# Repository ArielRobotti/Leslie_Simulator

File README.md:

# Leslie_Simulator

Electronic design project in Kicad commissioned by jayluo1 (Fiverr)

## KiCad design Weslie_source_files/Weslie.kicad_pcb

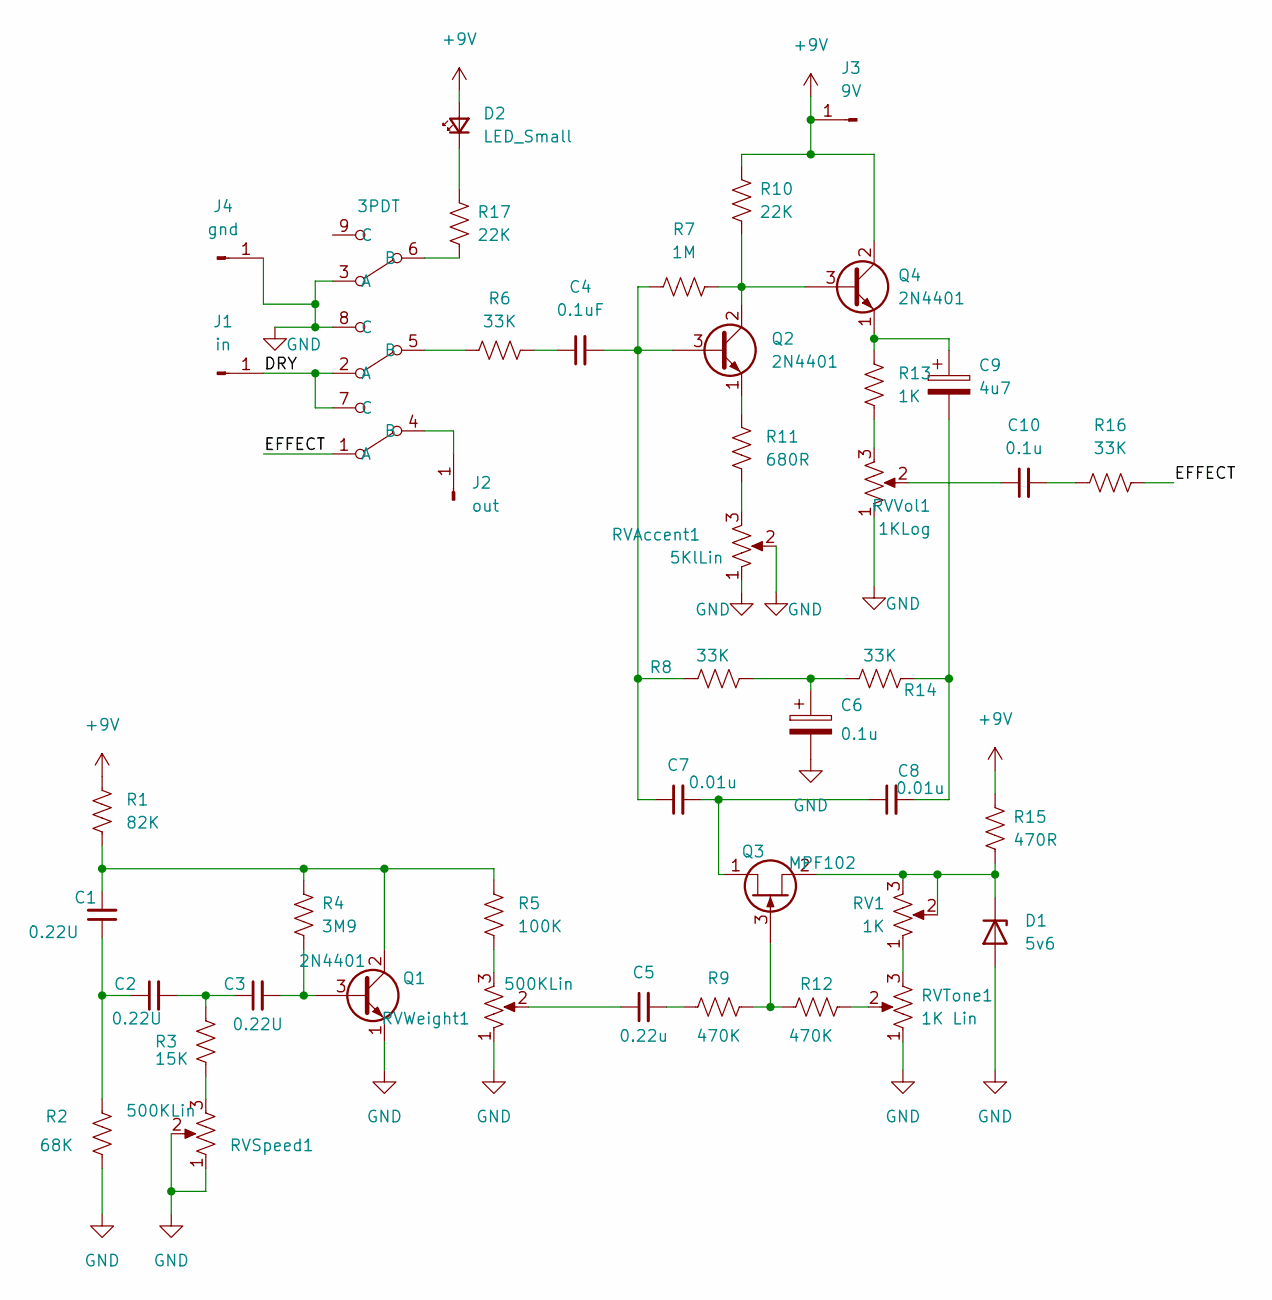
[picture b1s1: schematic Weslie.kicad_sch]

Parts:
C1, C2, C3: 0.22U; C_Disc_D10.0mm_W2.5mm_P5.00mm
C4: 0.1uF; C_Disc_D10.0mm_W2.5mm_P5.00mm
C5: 0.22u; C_Disc_D10.0mm_W2.5mm_P5.00mm
C6: 0.1u; CP_Radial_D5.0mm_P2.50mm
C7, C8: 0.01u; C_Disc_D10.0mm_W2.5mm_P5.00mm
C9: 4u7; CP_Radial_D5.0mm_P2.50mm
C10: 0.1u; C_Disc_D10.0mm_W2.5mm_P5.00mm
D1: 5v6; D_A-405_P7.62mm_Horizontal
D2: LED_Small; LED_D3.0mm
J1: in; Pin_D1.0mm_L10.0mm
J2: out; Pin_D1.0mm_L10.0mm
J3: 9V; Pin_D1.0mm_L10.0mm
J4: gnd; Pin_D1.0mm_L10.0mm
Q1, Q2, Q4: 2N4401; TO-92_Wide
Q3: MPF102; TO-92_Wide
R1: 82K; R_Axial_DIN0204_L3.6mm_D1.6mm_P7.62mm_Horizontal
R2: 68K; R_Axial_DIN0204_L3.6mm_D1.6mm_P7.62mm_Horizontal
R3: 15K; R_Axial_DIN0204_L3.6mm_D1.6mm_P7.62mm_Horizontal
R4: 3M9; R_Axial_DIN0204_L3.6mm_D1.6mm_P7.62mm_Horizontal
R5: 100K; R_Axial_DIN0204_L3.6mm_D1.6mm_P7.62mm_Horizontal
R6, R8, R14, R16: 33K; R_Axial_DIN0204_L3.6mm_D1.6mm_P7.62mm_Horizontal
R7: 1M; R_Axial_DIN0204_L3.6mm_D1.6mm_P7.62mm_Horizontal
R9, R12: 470K; R_Axial_DIN0204_L3.6mm_D1.6mm_P7.62mm_Horizontal
R10, R17: 22K; R_Axial_DIN0204_L3.6mm_D1.6mm_P7.62mm_Horizontal
R11: 680R; R_Axial_DIN0204_L3.6mm_D1.6mm_P7.62mm_Horizontal
R13: 1K; R_Axial_DIN0204_L3.6mm_D1.6mm_P7.62mm_Horizontal
R15: 470R; R_Axial_DIN0204_L3.6mm_D1.6mm_P7.62mm_Horizontal
RV1: 1K; Potentiometer_ACP_CA9-V10_Vertical_Hole
RVAccent1: 5KlLin; Potentiometer_Alps_RK09L_Single_Vertical
RVSpeed1: 500KLin; Potentiometer_Alps_RK09L_Single_Vertical
RVTone1: 1K Lin; Potentiometer_Alps_RK09L_Single_Vertical
RVVol1: 1KLog; Potentiometer_Alps_RK09L_Single_Vertical
RVWeight1: 500KLin; Potentiometer_Alps_RK09L_Single_Vertical
SW1: 3PDT; 3PD

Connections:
+9V: D2.2 (A), J3.1, Q4.2 (C), R1.2, R10.2, R15.2
/DRY: J1.1, SW1.2 (A), SW1.7 (C)
/EFFECT: R16.2, SW1.1 (A)
GND: C6.2, D1.2 (A), J4.1, Q1.1 (E), R2.1, RVAccent1.1, RVAccent1.2, RVSpeed1.1, RVSpeed1.2, RVTone1.1, RVVol1.1, RVWeight1.1, SW1.3 (A), SW1.8 (C)
unnamed: C1.1, C2.1, R2.2
unnamed: C1.2, Q1.2 (C), R1.1, R4.2, R5.2
unnamed: C2.2, C3.1, R3.2
unnamed: C3.2, Q1.3 (B), R4.1
unnamed: C4.1, R6.2
unnamed: C4.2, C7.1, Q2.3 (B), R7.1, R8.1
unnamed: C5.1, RVWeight1.2
unnamed: C5.2, R9.1
unnamed: C6.1, R8.2, R14.1
unnamed: C7.2, C8.1, Q3.1 (D)
unnamed: C8.2, C9.2, R14.2
unnamed: C9.1, Q4.1 (E), R13.2
unnamed: C10.1, RVVol1.2
unnamed: C10.2, R16.1
unnamed: D1.1 (K), Q3.2 (S), R15.1, RV1.2, RV1.3
unnamed: D2.1 (K), R17.2
unnamed: Q2.1 (E), R11.2
unnamed: Q2.2 (C), Q4.3 (B), R7.2, R10.1
unnamed: Q3.3 (G), R9.2, R12.1
unnamed: R3.1, RVSpeed1.3
unnamed: R5.1, RVWeight1.3
unnamed: R6.1, SW1.5 (B)
unnamed: R11.1, RVAccent1.3
unnamed: R12.2, RVTone1.2
unnamed: R13.1, RVVol1.3
unnamed: R17.1, SW1.6 (B)
unnamed: RV1.1, RVTone1.3
unnamed: J2.1, SW1.4 (B)

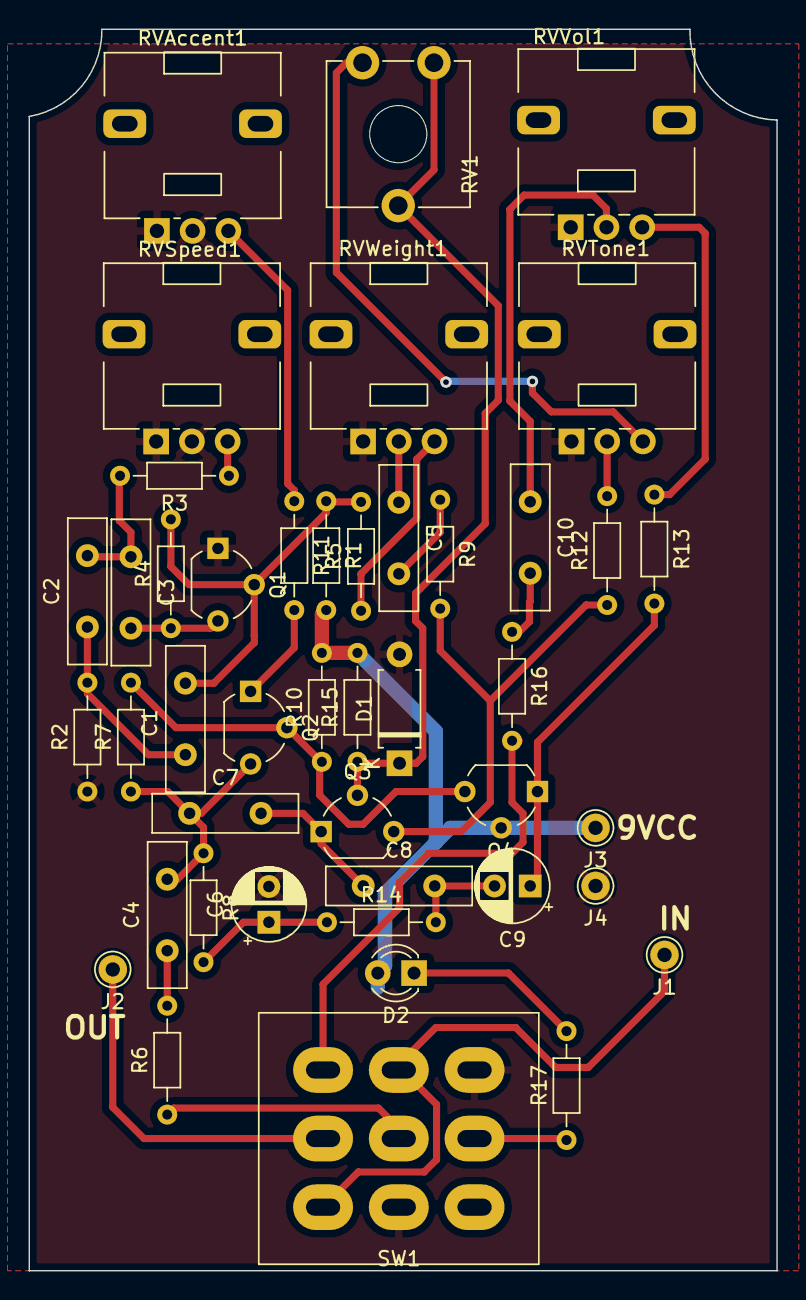
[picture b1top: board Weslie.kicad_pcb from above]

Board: 2 copper layers, 52.3 x 86.9 mm, 44 parts (0 on the bottom side), 32 nets.

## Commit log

2023-03-13 Cargando archivos
2023-03-13 Borrando archivos
2023-03-13 Schematic
2023-03-14 .gitignore
2023-03-15 Priemr entrega
2023-03-15 Primer entrega
